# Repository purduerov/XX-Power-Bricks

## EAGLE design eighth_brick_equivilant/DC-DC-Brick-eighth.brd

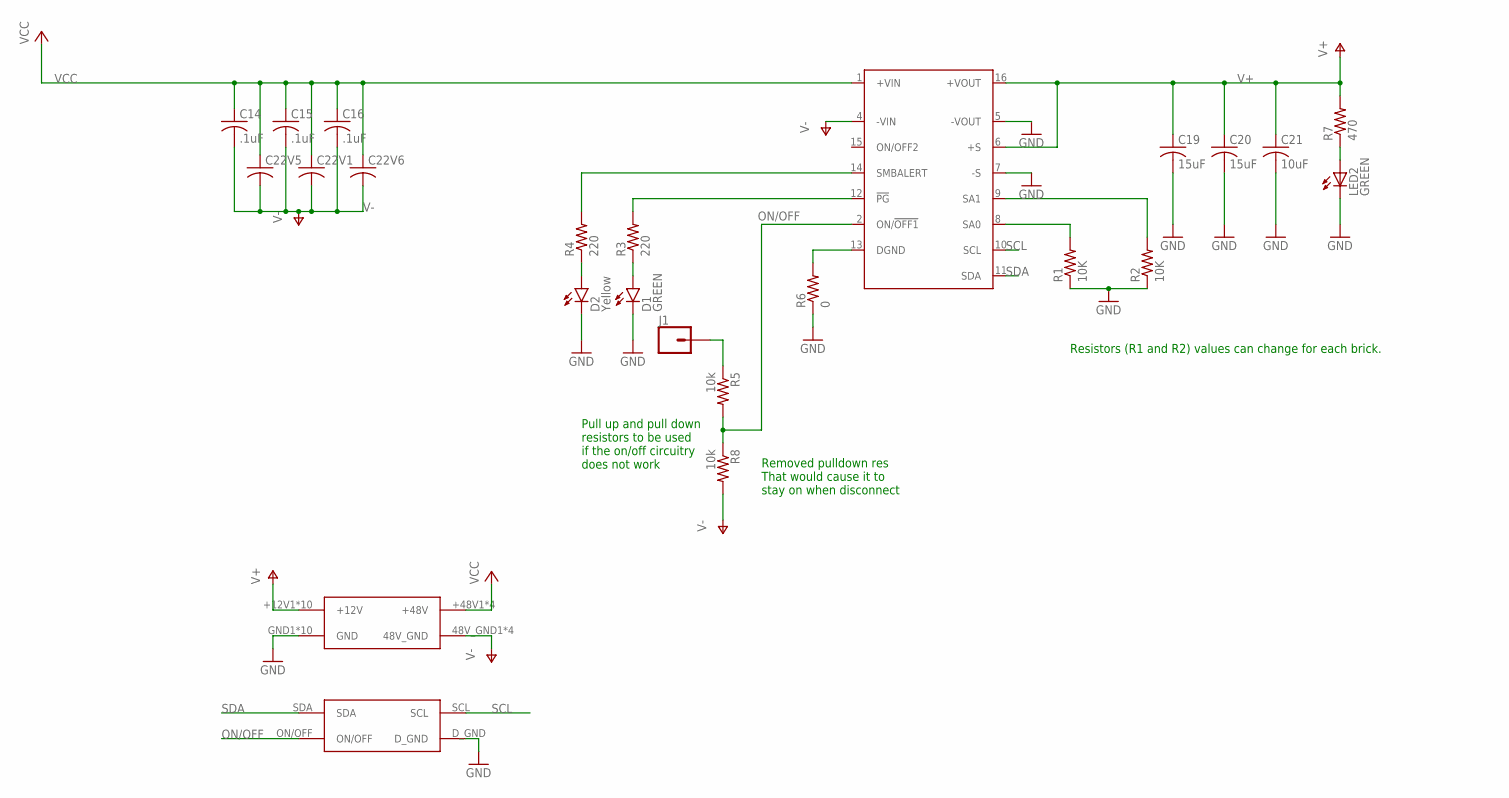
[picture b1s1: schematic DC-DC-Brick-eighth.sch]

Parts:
C14, C15, C16: .1uF; C0603
C19, C20: 15uF; C3216
C21: 10uF; C0603
C22V1, C22V5, C22V6: EXTENDED_PAD_CAPACITOR; MODIFIED-NICHICON-UX-8X10
D1: GREEN; LED-0603
D2: Yellow; LED-0603
J1: CONN_01; 1X01
LED2: GREEN; LED-0603; PARTNO 160-1446-1-ND
R1, R2: 10K; 0603-RES
R3, R4: 220; 0603-RES
R5, R8: 10k; 0603-RES
R6: 0; 0603-RES
R7: 470; 0603-RES
U$1: BRICK_DC-DC_CONVERTER_EIGHTH
U$4: BRICK_TO_POWER_DIST_WHOLE

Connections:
GND: C19.2, C20.2, C21.2, D1.C, D2.C, LED2.C, R1.1, R2.1, R6.1, U$1.5 (-VOUT), U$1.7 (-S), U$4.D_GND, U$4.GND1 (GND), U$4.GND2 (GND), U$4.GND3 (GND), U$4.GND4 (GND), U$4.GND5 (GND), U$4.GND6 (GND), U$4.GND7 (GND), U$4.GND8 (GND), U$4.GND9 (GND), U$4.GND10 (GND)
unnamed: R2.2, U$1.9 (SA1)
unnamed: R1.2, U$1.8 (SA0)
unnamed: R6.2, U$1.13 (DGND)
unnamed: D1.A, R3.1
unnamed: D2.A, R4.1
unnamed: R4.2, U$1.14 (SMBALERT)
unnamed: R3.2, U$1.12 (!PG)
unnamed: J1.1, R5.1
unnamed: LED2.A, R7.1
ON/OFF: R5.2, R8.1, U$1.2 (ON/!OFF1), U$4.ON/OFF
SCL: U$1.10 (SCL), U$4.SCL
SDA: U$1.11 (SDA), U$4.SDA
V+: C19.1, C20.1, C21.1, R7.2, U$1.6 (+S), U$1.16 (+VOUT), U$4.+12V1 (+12V), U$4.+12V2 (+12V), U$4.+12V3 (+12V), U$4.+12V4 (+12V), U$4.+12V5 (+12V), U$4.+12V6 (+12V), U$4.+12V7 (+12V), U$4.+12V8 (+12V), U$4.+12V9 (+12V), U$4.+12V10 (+12V)
V-: C14.2, C15.2, C16.2, C22V1.P$1 (4), C22V5.P$1 (4), C22V6.P$1 (4), R8.2, U$1.4 (-VIN), U$4.48V_GND1 (48V_GND), U$4.48V_GND2 (48V_GND), U$4.48V_GND3 (48V_GND), U$4.48V_GND4 (48V_GND)
VCC: C14.1, C15.1, C16.1, C22V1.P$3 (3), C22V5.P$3 (3), C22V6.P$3 (3), U$1.1 (+VIN), U$4.+48V1 (+48V), U$4.+48V2 (+48V), U$4.+48V3 (+48V), U$4.+48V4 (+48V)

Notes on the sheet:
Removed pulldown res That would cause it to stay on when disconnect
Resistors (R1 and R2) values can change for each brick.
Pull up and pull down resistors to be used if the on/off circuitry does not work

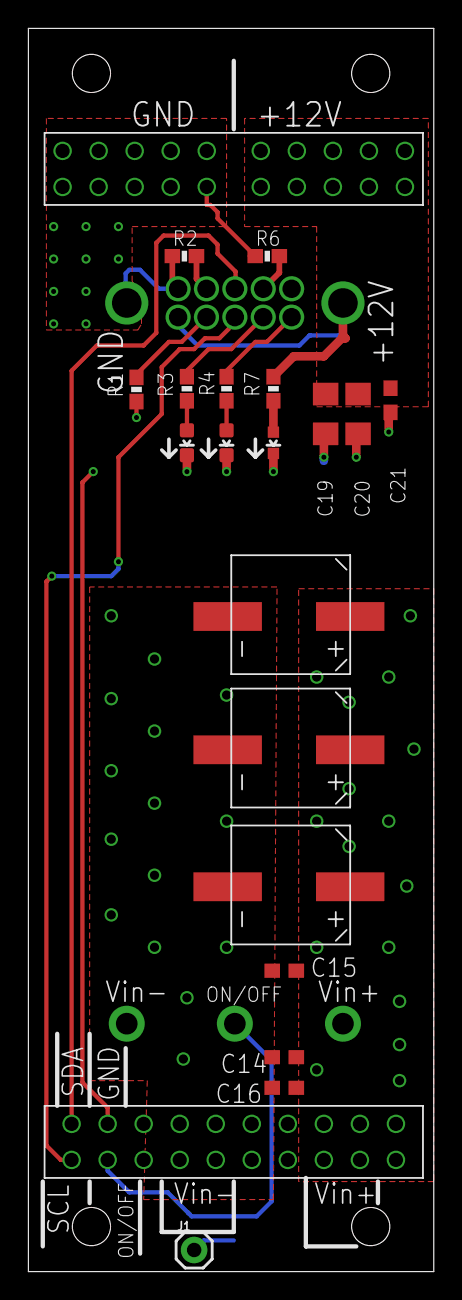
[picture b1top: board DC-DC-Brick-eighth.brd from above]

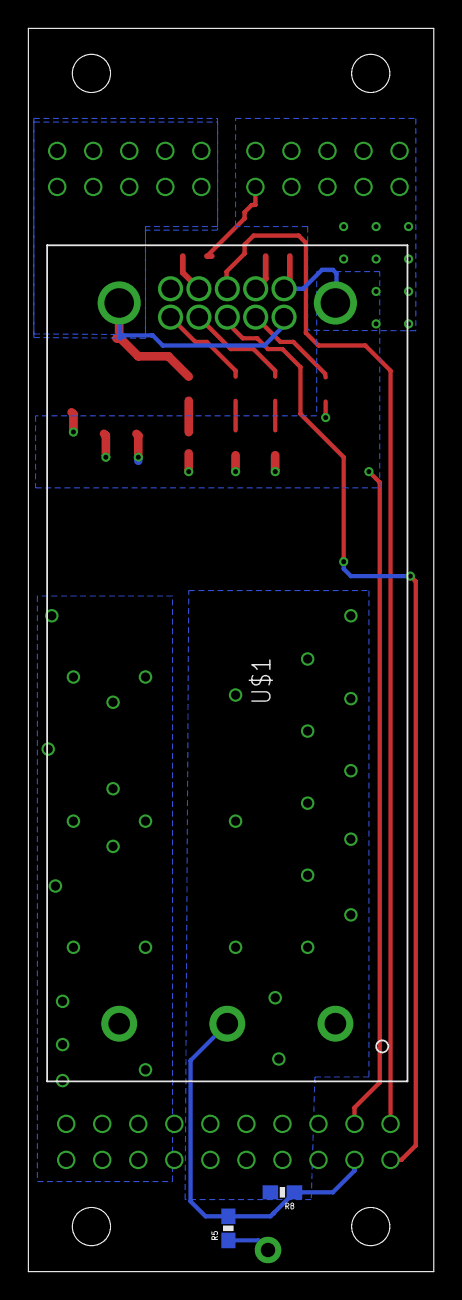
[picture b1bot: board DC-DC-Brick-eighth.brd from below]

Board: 2 copper layers, 28.6 x 87.6 mm, 23 parts (3 on the bottom side), 16 nets.

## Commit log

2017-09-28 initial
2017-10-15 Added gitignore
2017-11-17 Power brick connectors edited
2017-12-01 New power brick board
2017-12-03 Edit Signal Name
2017-12-03 fixed 48V_return on layout
2017-12-24 Created a version of the power bricks board for the eighth brick
2017-12-28 Added mounting holes to circuit board
2017-12-30 Made the eighth brick thinner
2018-01-04 Fixing few issues with power brick
2018-01-06 Addressing comments and adding silk screen
2018-01-10 Version submitted to elecrow
2018-12-30 repositioned the capacitors
    fixed the board up

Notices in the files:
parts and their libraries:
SparkFun-LED: Licensing: Creative Commons ShareAlike 4.0 International - https://creativecommons.org/licenses/by-sa/4.0
SparkFun: Licensing: CC v3.0 Share-Alike You are welcome to use this library for commercial purposes.
